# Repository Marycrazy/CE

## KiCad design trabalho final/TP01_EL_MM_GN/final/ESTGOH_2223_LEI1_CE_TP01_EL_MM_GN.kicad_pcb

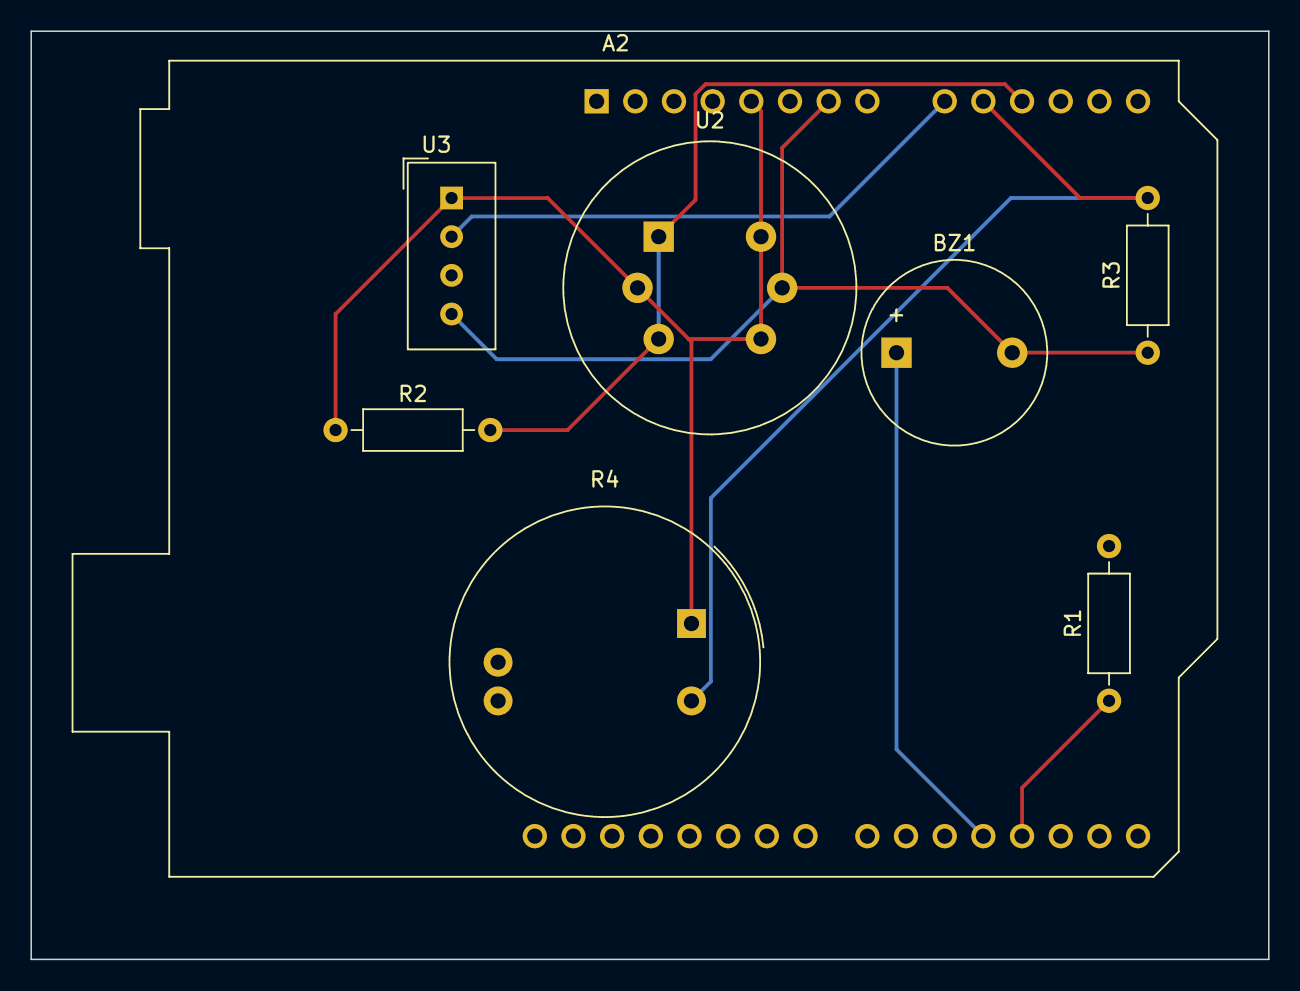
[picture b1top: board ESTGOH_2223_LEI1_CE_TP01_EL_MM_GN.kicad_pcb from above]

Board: 2 copper layers, 81.3 x 61.0 mm, 8 parts (0 on the bottom side), 7 nets.

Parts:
A2: Arduino_UNO_R2
BZ1: Buzzer; Buzzer_12x9.5RM7.6
R1, R2, R3: 560; R_Axial_DIN0207_L6.3mm_D2.5mm_P10.16mm_Horizontal
R4: R_Photo; LuminOX_LOX-O2
U2: MQ-6
U3: CHT11; Aosong_DHT11_5.5x12.0_P2.54mm

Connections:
0: A2.7 (GND), BZ1.2 (+), R3.1, U2.5 (VH-), U3.4 (GND)
+5V: A2.5 (+5V), R2.1, R4.1, U2.2 (VH+), U2.4 (A2), U2.6 (A1), U3.1 (VCC)
unnamed: A2.9 (A0), U3.2 (IO)
unnamed: A2.10 (A1), R3.2, R4.2
unnamed: A2.11 (A2), R2.2, U2.1 (B1), U2.3 (B2)
unnamed: A2.18 (D3), R1.1
unnamed: A2.19 (D4), BZ1.1 (-)
